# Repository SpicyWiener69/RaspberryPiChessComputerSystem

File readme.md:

### Chess Computer System based on a Raspberry Pi

## Folder Descriptions
```
.
├── UI/:    Chess UI frontend. Allows players to adjust game settings.
├── core/:  program entry point. Handles game logic.
├── ChessBoardPCB/: A PCB board with hall effect sensors designed to sense the position of a chess game. Designed in Kicad7.
└── hardware/: BOM, 3d design files of the system. Designed in Fusion360.
```
More info is written at every subfolder's readme.md file.

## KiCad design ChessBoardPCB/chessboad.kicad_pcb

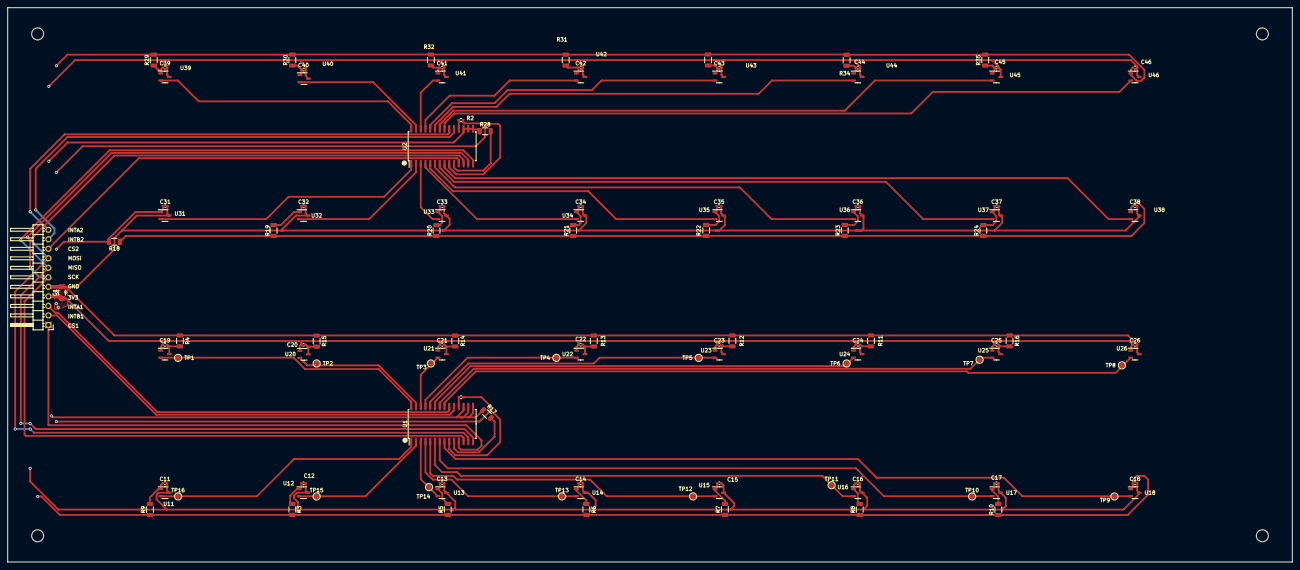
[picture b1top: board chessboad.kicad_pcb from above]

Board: 2 copper layers, 343.0 x 148.0 mm, 120 parts (0 on the bottom side), 45 nets.

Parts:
C1: 10uF; C_1206_3216Metric_Pad1.33x1.80mm_HandSolder
C11, C12, C13, C14, C15, C16, C17, C18, C19, C20, C21, C22, C23, C24, C25, C26, C31, C32, C33, C34, C35, C36, C37, C38, C39, C40, C41, C42, C43, C44, C45, C46: 100nF; C_0402_1005Metric_Pad0.74x0.62mm_HandSolder
H1, H2, H3, H4: MountingHole; MountingHole_3.2mm_M3_ISO7380
J1: Conn_01x11_Pin; PinHeader_1x11_P2.54mm_Horizontal
R1, R2: 10k; R_0402_1005Metric_Pad0.72x0.64mm_HandSolder
R3, R4, R5, R6, R7, R8, R9, R10, R11, R12, R13, R14, R15, R16, R17, R18, R19, R20, R21, R22, R23, R24, R28, R29, R30, R31, R32, R33, R34, R35: R; R_1206_3216Metric
TP1, TP2, TP3, TP4, TP5, TP6, TP7, TP8, TP9, TP10, TP11, TP12, TP13, TP14, TP15, TP16: TestPoint; TestPoint_Pad_D1.5mm
U1, U2: MCP23S17_SO; SOIC-28W_7.5x17.9mm_P1.27mm
U11, U12, U13, U14, U15, U16, U17, U18, U19, U20, U21, U22, U23, U24, U25, U26, U31, U32, U33, U34, U35, U36, U37, U38, U39, U40, U41, U42, U43, U44, U45, U46: TMAG4231; SOT-23-3

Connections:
+3.3V: C1.1, C11.1, C12.1, C13.1, C14.1, C15.1, C16.1, C17.1, C18.1, C19.1, C20.1, C21.1, C22.1, C23.1, C24.1, C25.1, C26.1, C31.1, C32.1, C33.1, C34.1, C35.1, C36.1, C37.1, C38.1, C39.1, C40.1, C41.1, C42.1, C43.1, C44.1, C45.1, C46.1, J1.4, R1.1, R2.1, R3.1, R3.2, R5.1, R5.2, R6.1, R6.2, R7.1, R7.2, R8.1, R8.2, R9.1, R9.2, R10.1, R10.2, R18.1, R18.2, R19.1, R19.2, R20.1, R20.2, R21.1, R21.2, R22.1, R22.2, R23.1, R23.2, R24.1, R24.2, R29.1, R29.2, R30.1, R30.2, R31.1, R31.2, R32.1, R32.2, R33.1, R33.2, R34.1, R34.2, R35.1, R35.2, U1.9 (VDD), U2.9 (VDD), U11.1 (Vcc), U12.1 (Vcc), U13.1 (Vcc), U14.1 (Vcc), U15.1 (Vcc), U16.1 (Vcc), U17.1 (Vcc), U18.1 (Vcc), U19.1 (Vcc), U20.1 (Vcc), U21.1 (Vcc), U22.1 (Vcc), U23.1 (Vcc), U24.1 (Vcc), U25.1 (Vcc), U26.1 (Vcc), U31.1 (Vcc), U32.1 (Vcc), U33.1 (Vcc), U34.1 (Vcc), U35.1 (Vcc), U36.1 (Vcc), U37.1 (Vcc), U38.1 (Vcc), U39.1 (Vcc), U40.1 (Vcc), U41.1 (Vcc), U42.1 (Vcc), U43.1 (Vcc), U44.1 (Vcc), U45.1 (Vcc), U46.1 (Vcc)
/CS1: J1.1, U1.11 (~CS)
/CS2: J1.9, U2.11 (~CS)
/INTA1: J1.3, U1.20 (INTA)
/INTA2: J1.11, U2.20 (INTA)
/INTB1: J1.2, U1.19 (INTB)
/INTB2: J1.10, U2.19 (INTB)
/MISO: J1.7, U1.14 (SO), U2.14 (SO)
/MOSI: J1.8, U1.13 (SI), U2.13 (SI)
/SCK: J1.6, U1.12 (SCK), U2.12 (SCK)
GND: C1.2, C11.2, C12.2, C13.2, C14.2, C15.2, C16.2, C17.2, C18.2, C19.2, C20.2, C21.2, C22.2, C23.2, C24.2, C25.2, C26.2, C31.2, C32.2, C33.2, C34.2, C35.2, C36.2, C37.2, C38.2, C39.2, C40.2, C41.2, C42.2, C43.2, C44.2, C45.2, C46.2, J1.5, R4.1, R4.2, R11.1, R11.2, R12.1, R12.2, R13.1, R13.2, R14.1, R14.2, R15.1, R15.2, R16.1, R16.2, R17.1, R17.2, R28.1, R28.2, U1.10 (VSS), U1.15 (A0), U1.16 (A1), U1.17 (A2), U2.10 (VSS), U2.15 (A0), U2.16 (A1), U2.17 (A2), U11.3 (GND), U12.3 (GND), U13.3 (GND), U14.3 (GND), U15.3 (GND), U16.3 (GND), U17.3 (GND), U18.3 (GND), U19.3 (GND), U20.3 (GND), U21.3 (GND), U22.3 (GND), U23.3 (GND), U24.3 (GND), U25.3 (GND), U26.3 (GND), U31.3 (GND), U32.3 (GND), U33.3 (GND), U34.3 (GND), U35.3 (GND), U36.3 (GND), U37.3 (GND), U38.3 (GND), U39.3 (GND), U40.3 (GND), U41.3 (GND), U42.3 (GND), U43.3 (GND), U44.3 (GND), U45.3 (GND), U46.3 (GND)
unnamed: R1.2, U1.18 (~RESET)
unnamed: R2.2, U2.18 (~RESET)
U1A0: TP8.1, U1.21 (GPA0), U26.2 (OUT)
U1A1: TP7.1, U1.22 (GPA1), U25.2 (OUT)
U1A2: TP6.1, U1.23 (GPA2), U24.2 (OUT)
U1A3: TP5.1, U1.24 (GPA3), U23.2 (OUT)
U1A4: TP4.1, U1.25 (GPA4), U22.2 (OUT)
U1A5: TP3.1, U1.26 (GPA5), U21.2 (OUT)
U1A6: TP2.1, U1.27 (GPA6), U20.2 (OUT)
U1A7: TP1.1, U1.28 (GPA7), U19.2 (OUT)
U1B0: TP16.1, U1.1 (GPB0), U11.2 (OUT)
U1B1: TP15.1, U1.2 (GPB1), U12.2 (OUT)
U1B2: TP14.1, U1.3 (GPB2), U13.2 (OUT)
U1B3: TP13.1, U1.4 (GPB3), U14.2 (OUT)
U1B4: TP12.1, U1.5 (GPB4), U15.2 (OUT)
U1B5: TP11.1, U1.6 (GPB5), U16.2 (OUT)
U1B6: TP10.1, U1.7 (GPB6), U17.2 (OUT)
U1B7: TP9.1, U1.8 (GPB7), U18.2 (OUT)
U2A0: U2.21 (GPA0), U46.2 (OUT)
U2A1: U2.22 (GPA1), U45.2 (OUT)
U2A2: U2.23 (GPA2), U44.2 (OUT)
U2A3: U2.24 (GPA3), U43.2 (OUT)
U2A4: U2.25 (GPA4), U42.2 (OUT)
U2A5: U2.26 (GPA5), U41.2 (OUT)
U2A6: U2.27 (GPA6), U40.2 (OUT)
U2A7: U2.28 (GPA7), U39.2 (OUT)
U2B0: U2.1 (GPB0), U31.2 (OUT)
U2B1: U2.2 (GPB1), U32.2 (OUT)
U2B2: U2.3 (GPB2), U33.2 (OUT)
U2B3: U2.4 (GPB3), U34.2 (OUT)
U2B4: U2.5 (GPB4), U35.2 (OUT)
U2B5: U2.6 (GPB5), U36.2 (OUT)
U2B6: U2.7 (GPB6), U37.2 (OUT)
U2B7: U2.8 (GPB7), U38.2 (OUT)

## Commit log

2025-11-29 Squashed 'UI/' content from commit c58a90c
    git-subtree-dir: UI
    git-subtree-split: c58a90c38e5471ac482c5bf0ad6a405526e563a0
2025-11-30 Squashed 'core/' content from commit 208fcae
    git-subtree-dir: core
    git-subtree-split: 208fcaecba1569564364a0aa819b507b2dd71682
2025-11-30 Update README with setup and configuration instructions
    Added setup instructions for Python environment and driver configuration.
2025-11-30 Squashed 'ChessBoardPCB/' content from commit bf86e3c
    git-subtree-dir: ChessBoardPCB
    git-subtree-split: bf86e3c46192cbacb9a914b650b1113062c648df
2025-11-30 fixed lvgl dependency
2025-12-01 added redo move warning ui
2025-12-02 Revise README for Chess UI project using LVGL
2025-12-02 Update README with folder descriptions and cleanup
    Added folder descriptions for project structure and removed outdated configuration instructions.
2025-12-05 changes to UI
2025-12-05 new reset socket message passing
2025-12-12 removed old stuff
2025-12-12 Squashed 'core/' content from commit 6f04aa3
    git-subtree-dir: core
    git-subtree-split: 6f04aa3a95033adeb8a05d3d1506cb000160d5df
2025-12-12 cleanup
2025-12-12 better state handling
2025-12-12 fixed ui black/white bug
2025-12-12 refactor diff_board_array_to_event to board_event_handler.py file
2025-12-16 2nd pcb intergration, success.
2025-12-23 fixed bug at square e4, added new wait state for manual intervention on semi-auto chess system
2025-12-24 Add auto mover feature and refactor game setup handling
2026-01-06 added logging argparse. not implemented yet
2026-01-06 Update README files to include Python environment setup instructions and clarify hardware descriptions
2026-01-06 migrating to uv, testing
2026-01-22 refactored so board_event_handler won't modify chessboard obj
2026-01-31 added pathfinding algorithm file. added matplotlib to uv dependencies.
2026-01-31 added UciMove return
2026-01-31 added functionality so "take" moves work in any order.
2026-01-31 flatten, refactered class structures.
